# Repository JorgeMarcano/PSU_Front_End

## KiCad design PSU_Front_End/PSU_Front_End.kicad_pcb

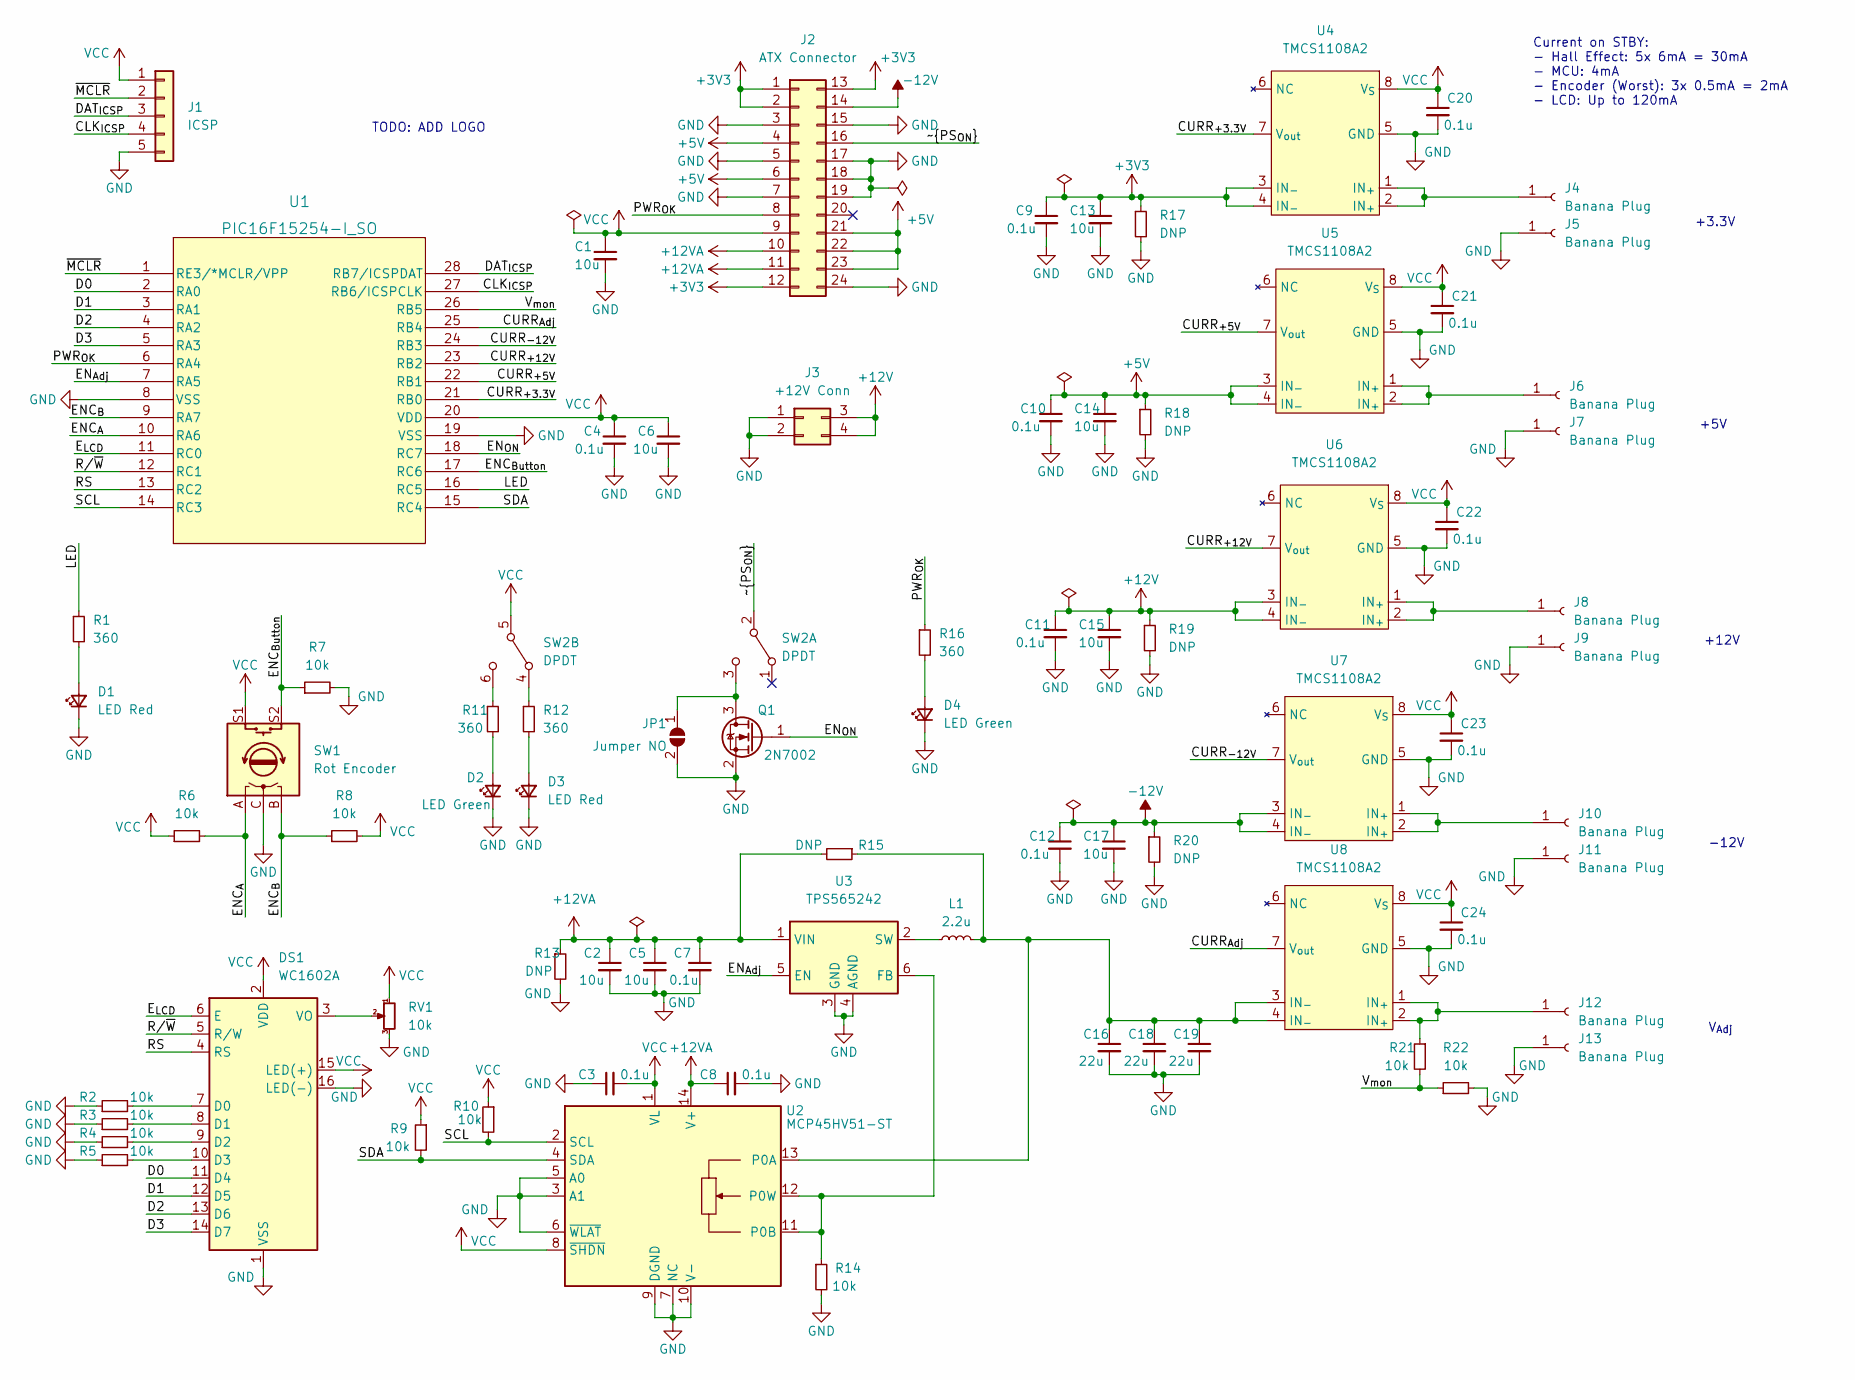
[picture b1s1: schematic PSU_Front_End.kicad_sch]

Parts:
C1, C2, C5, C6, C13, C14, C15, C17: 10u; C_0805_2012Metric_Pad1.18x1.45mm_HandSolder; MFG PN 1276-2891-1-ND
C3, C4, C7, C8, C9, C10, C11, C12, C20, C21, C22, C23, C24: 0.1u; C_0805_2012Metric_Pad1.18x1.45mm_HandSolder; MFG PN 1276-1099-1-ND
C16, C18, C19: 22u; C_0805_2012Metric_Pad1.18x1.45mm_HandSolder; MFG PN 1276-CL21A226MAYNNNECT-ND
D1, D3: LED Red; LED_0603_1608Metric_Pad1.05x0.95mm_HandSolder; MFG PN 3147-B1931USD-20D000814U1930CT-ND
D2, D4: LED Green; LED_0603_1608Metric_Pad1.05x0.95mm_HandSolder; MFG PN 3147-B1931NG--20D001114U1930CT-ND
DS1: WC1602A; MFG PN 4411-CN0293-ND
J1: ICSP; PinHeader_1x05_P2.54mm_Vertical
J2: ATX Connector; Molex_Mini-Fit_Jr_5566-24A2_2x12_P4.20mm_Vertical; MFG PN 23-0039299247-ND
J3: +12V Conn; Molex_Mini-Fit_Jr_5566-04A2_2x02_P4.20mm_Vertical; MFG PN WM7325-ND
J4, J5, J6, J7, J8, J9, J10, J11, J12, J13: Banana Plug; Banana_Jack_1Pin
JP1: Jumper NO; SolderJumper-2_P1.3mm_Open_RoundedPad1.0x1.5mm
L1: 2.2u; L_Abracon_ASPI-0630LR; MFG PN 553-BMRA000606302R2MA1CT-ND
Q1: 2N7002; SOT-23; MFG PN 1727-8643-1-ND
R1, R11, R12, R16: 360; R_0805_2012Metric_Pad1.20x1.40mm_HandSolder; MFG PN 738-RMCF0805FT360RCT-ND
R2, R3, R4, R5, R6, R7, R8, R9, R10, R14, R21, R22: 10k; R_0805_2012Metric_Pad1.20x1.40mm_HandSolder; MFG PN RMCF0805FT10K0CT-ND
R13, R15, R17, R18, R19, R20: DNP; R_Axial_DIN0309_L9.0mm_D3.2mm_P12.70mm_Horizontal
RV1: 10k; TrimPot; MFG PN 119-06TR4DA103CP-ND
SW1: Rot Encoder; RotaryEncoder_Alps_EC12E-Switch_Vertical_H20mm; MFG PN PEC12R-4130F-S0012-ND
SW2: DPDT; SW DPDT; MFG PN 2449-ANT21SECQE-ND
U1: PIC16F15254-I_SO; SOIC-28W_7.5x18.7mm_P1.27mm; MFG PN 150-PIC16F15254-I/SO-ND
U2: MCP45HV51-ST; TSSOP-14_4.4x5mm_P0.65mm; MFG PN MCP45HV51-104E/ST-ND
U3: TPS565242; SOT-563; MFG PN 296-TPS565242DRLRCT-ND
U4, U5, U6, U7, U8: TMCS1108A2; SOIC-8-Wider; MFG PN 296-TMCS1108A2BQDTCT-ND

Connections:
+3V3: C9.1, C13.1, J2.1, J2.2, J2.12, J2.13, R17.1, U4.3 (IN_{-}), U4.4 (IN_{-})
+5V: C10.1, C14.1, J2.4, J2.6, J2.21, J2.22, J2.23, R18.1, U5.3 (IN_{-}), U5.4 (IN_{-})
+12V: C11.1, C15.1, J3.3, J3.4, R19.1, U6.3 (IN_{-}), U6.4 (IN_{-})
+12VA: C2.1, C5.1, C7.1, C8.1, J2.10, J2.11, R13.1, R15.2, U2.14 (V+), U3.1 (VIN)
-12V: C12.1, C17.1, J2.14, R20.1, U7.3 (IN_{-}), U7.4 (IN_{-})
/CLK_{ICSP}: J1.4, U1.27 (RB6/ICSPCLK)
/CURR_{+3.3V}: U1.21 (RB0), U4.7 (V_{out})
/CURR_{+5V}: U1.22 (RB1), U5.7 (V_{out})
/CURR_{+12V}: U1.23 (RB2), U6.7 (V_{out})
/CURR_{-12V}: U1.24 (RB3), U7.7 (V_{out})
/CURR_{Adj}: U1.25 (RB4), U8.7 (V_{out})
/D0: DS1.11 (D4), U1.2 (RA0)
/D1: DS1.12 (D5), U1.3 (RA1)
/D2: DS1.13 (D6), U1.4 (RA2)
/D3: DS1.14 (D7), U1.5 (RA3)
/DAT_{ICSP}: J1.3, U1.28 (RB7/ICSPDAT)
/ENC_{A}: R6.2, SW1.A, U1.10 (RA6)
/ENC_{Button}: R7.1, SW1.S2, U1.17 (RC6)
/ENC_{B}: R8.1, SW1.B, U1.9 (RA7)
/EN_{Adj}: U1.7 (RA5), U3.5 (EN)
/EN_{ON}: Q1.1 (G), U1.18 (RC7)
/E_{LCD}: DS1.6 (E), U1.11 (RC0)
/LED: R1.1, U1.16 (RC5)
/PWR_{OK}: J2.8, R16.1, U1.6 (RA4)
/RS: DS1.4 (RS), U1.13 (RC2)
/R/~W: DS1.5 (R/W), U1.12 (RC1)
/SCL: R10.2, U1.14 (RC3), U2.2 (SCL)
/SDA: R9.2, U1.15 (RC4), U2.4 (SDA)
/V_{mon}: R21.2, R22.1, U1.26 (RB5)
/~MCLR: J1.2, U1.1 (RE3/*MCLR/VPP)
/~PS_{ON}: J2.16, SW2.2 (B)
GND: C1.2, C2.2, C3.1, C4.2, C5.2, C6.2, C7.2, C8.2, C9.2, C10.2, C11.2, C12.2, C13.2, C14.2, C15.2, C16.2, C17.2, C18.2, C19.2, C20.2, C21.2, C22.2, C23.2, C24.2, D1.1 (K), D2.1 (K), D3.1 (K), D4.1 (K), DS1.1 (VSS), DS1.16 (LED(-)), J1.5, J2.3, J2.5, J2.7, J2.15, J2.17, J2.18, J2.19, J2.24, J3.1, J3.2, J5.1, J7.1, J9.1, J11.1, J13.1, JP1.2 (B), Q1.2 (S), R2.1, R3.1, R4.1, R5.1, R7.2, R13.2, R14.2, R17.2, R18.2, R19.2, R20.2, R22.2, RV1.3, SW1.C, U1.8 (VSS), U1.19 (VSS), U2.3 (A1), U2.5 (A0), U2.6 (~WLAT), U2.7 (NC), U2.9 (DGND), U2.10 (V-), U3.3 (GND), U3.4 (AGND), U4.5 (GND), U5.5 (GND), U6.5 (GND), U7.5 (GND), U8.5 (GND)
unnamed: C16.1, C18.1, C19.1, L1.2, R15.1, U2.13 (P0A), U8.3 (IN_{-}), U8.4 (IN_{-})
unnamed: D1.2 (A), R1.2
unnamed: D2.2 (A), R11.2
unnamed: D3.2 (A), R12.2
unnamed: D4.2 (A), R16.2
unnamed: DS1.3 (VO), RV1.2
unnamed: DS1.7 (D0), R2.2
unnamed: DS1.8 (D1), R3.2
unnamed: DS1.9 (D2), R4.2
unnamed: DS1.10 (D3), R5.2
unnamed: J4.1, U4.1 (IN_{+}), U4.2 (IN_{+})
unnamed: J6.1, U5.1 (IN_{+}), U5.2 (IN_{+})
unnamed: J8.1, U6.1 (IN_{+}), U6.2 (IN_{+})
unnamed: J10.1, U7.1 (IN_{+}), U7.2 (IN_{+})
unnamed: J12.1, R21.1, U8.1 (IN_{+}), U8.2 (IN_{+})
unnamed: JP1.1 (A), Q1.3 (D), SW2.3 (C)
unnamed: L1.1, U3.2 (SW)
unnamed: R11.1, SW2.6 (C)
unnamed: R12.1, SW2.4 (A)
unnamed: R14.1, U2.11 (P0B), U2.12 (P0W), U3.6 (FB)
VCC: C1.1, C3.2, C4.1, C6.1, C20.1, C21.1, C22.1, C23.1, C24.1, DS1.2 (VDD), DS1.15 (LED(+)), J1.1, J2.9, R6.1, R8.2, R9.1, R10.1, RV1.1, SW1.S1, SW2.5 (B), U1.20 (VDD), U2.1 (VL), U2.8 (~SHDN), U4.8 (V_{S}), U5.8 (V_{S}), U6.8 (V_{S}), U7.8 (V_{S}), U8.8 (V_{S})

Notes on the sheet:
+12V
-12V
+3.3V
TODO: ADD LOGO
V_{Adj}
Current on STBY: - Hall Effect: 5x 6mA = 30mA - MCU: 4mA - Encoder (Worst): 3x 0.5mA = 2mA - LCD: Up to 120mA
+5V

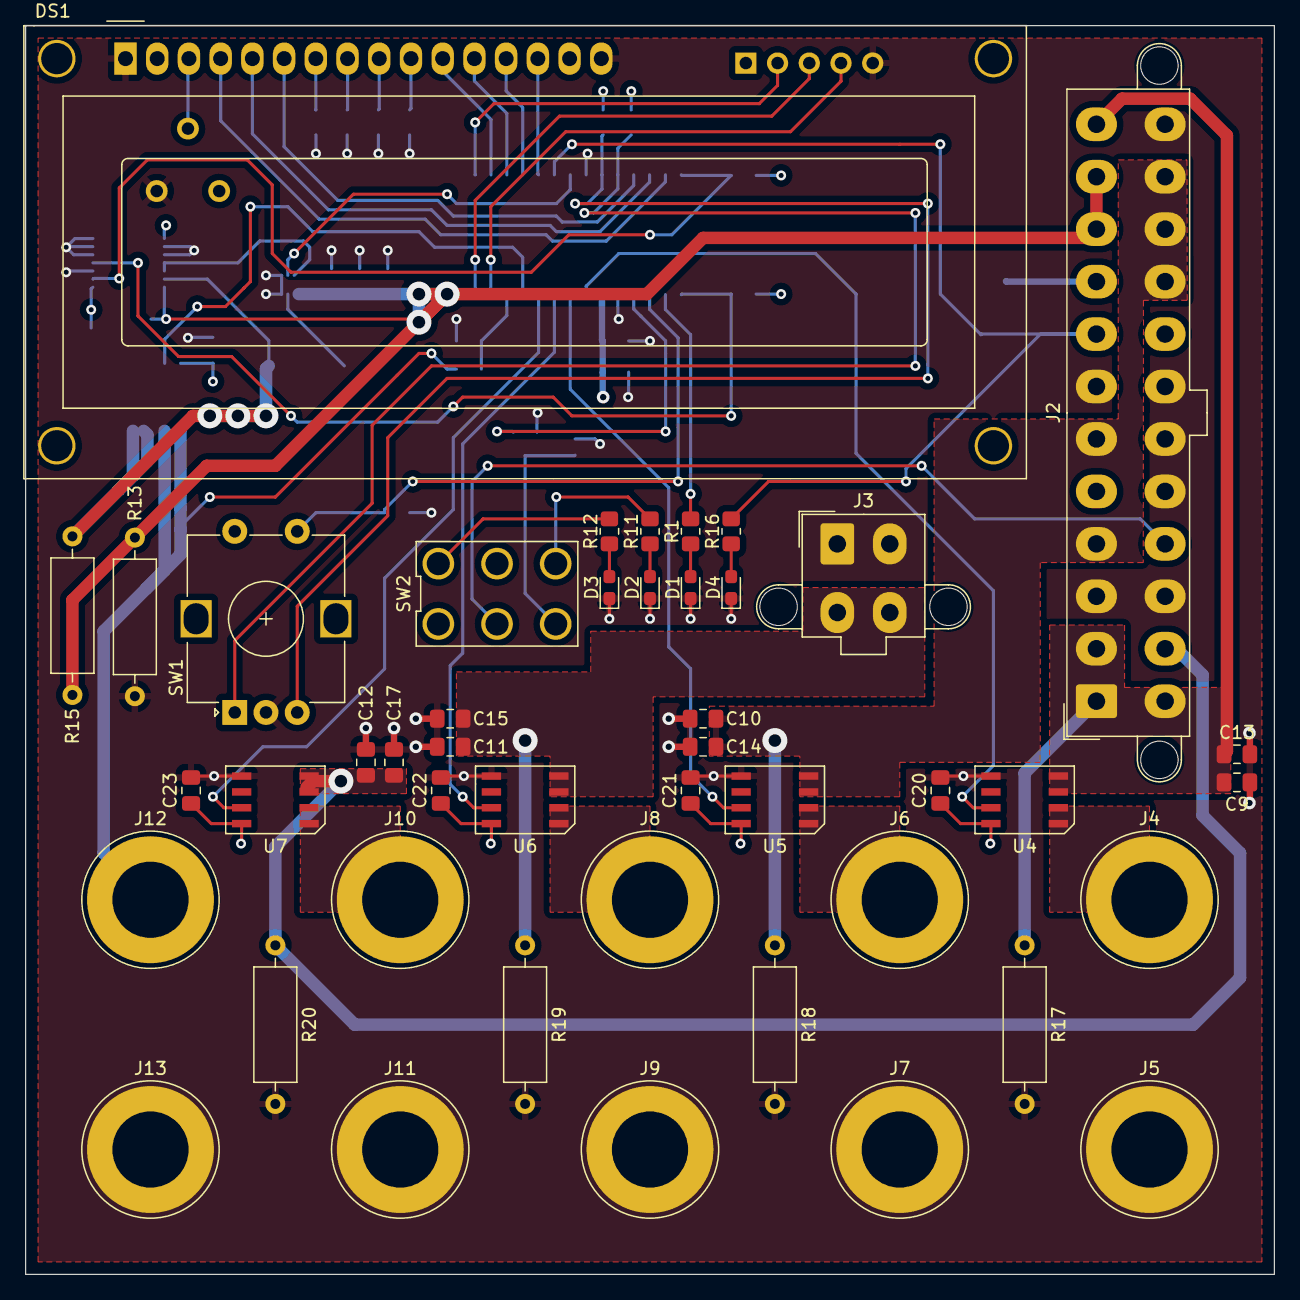
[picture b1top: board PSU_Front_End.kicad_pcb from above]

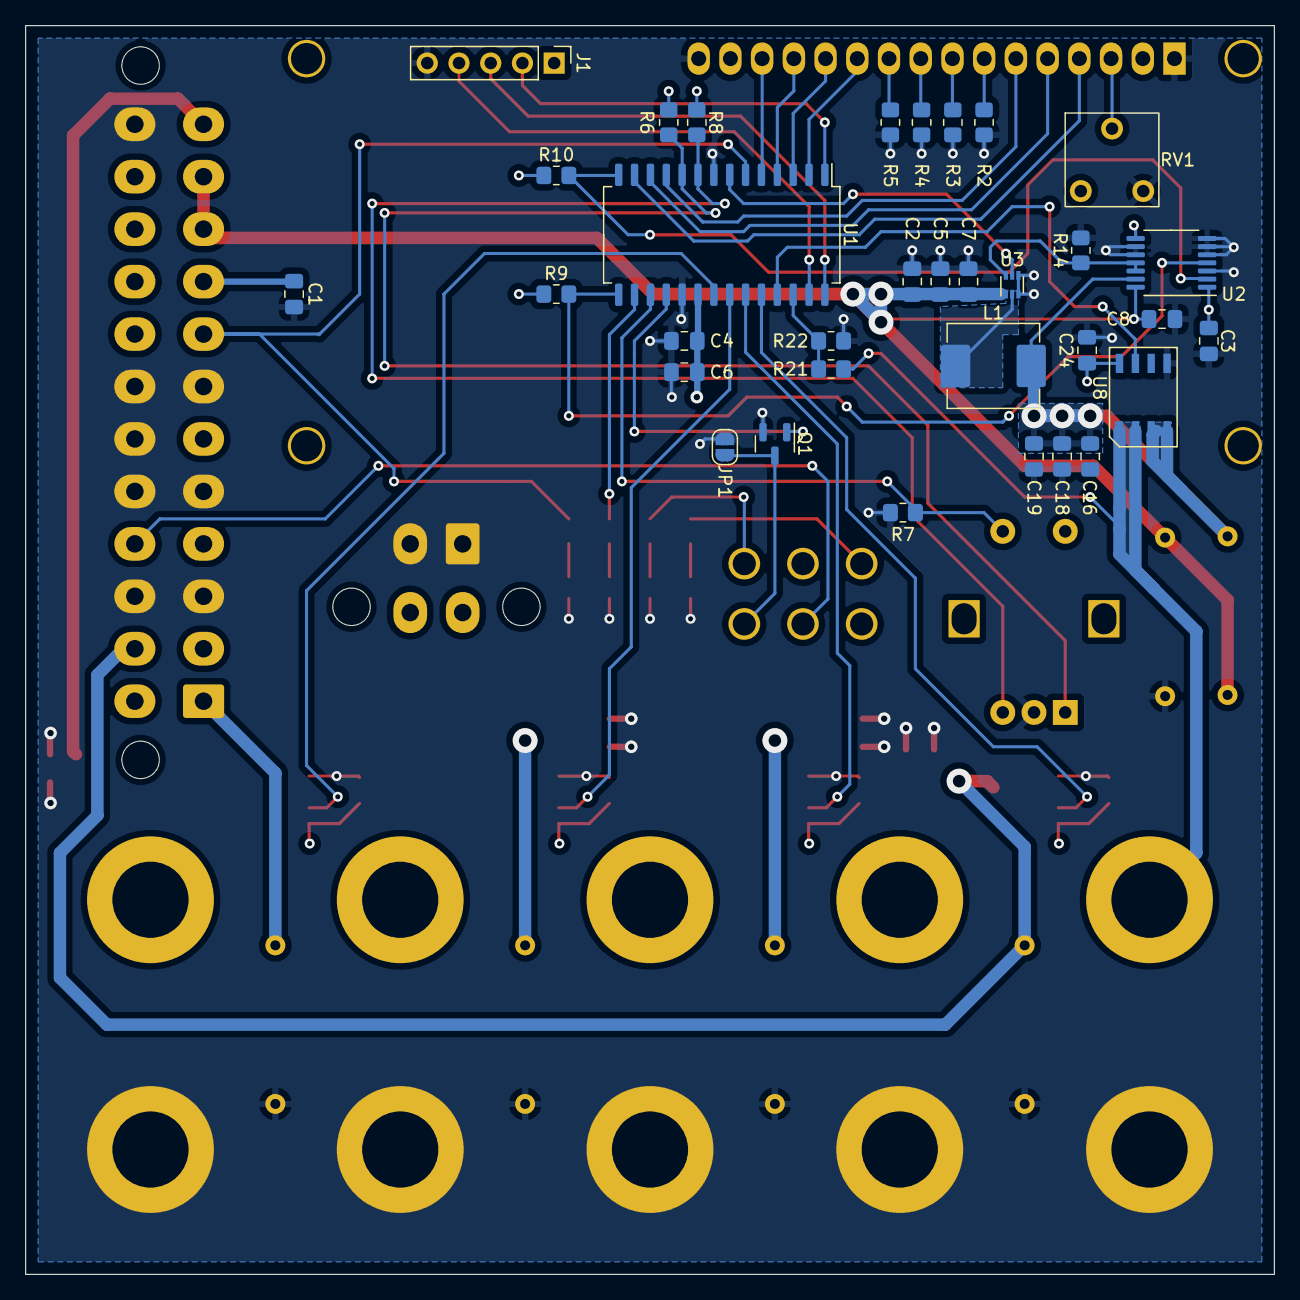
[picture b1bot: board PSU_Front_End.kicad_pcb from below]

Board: 4 copper layers, 100.0 x 100.0 mm, 78 parts (33 on the bottom side), 53 nets.

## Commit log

2024-05-03 Schematic Done
    Schematic Done and almost done BOM
2024-05-07 Finished Board Layout
